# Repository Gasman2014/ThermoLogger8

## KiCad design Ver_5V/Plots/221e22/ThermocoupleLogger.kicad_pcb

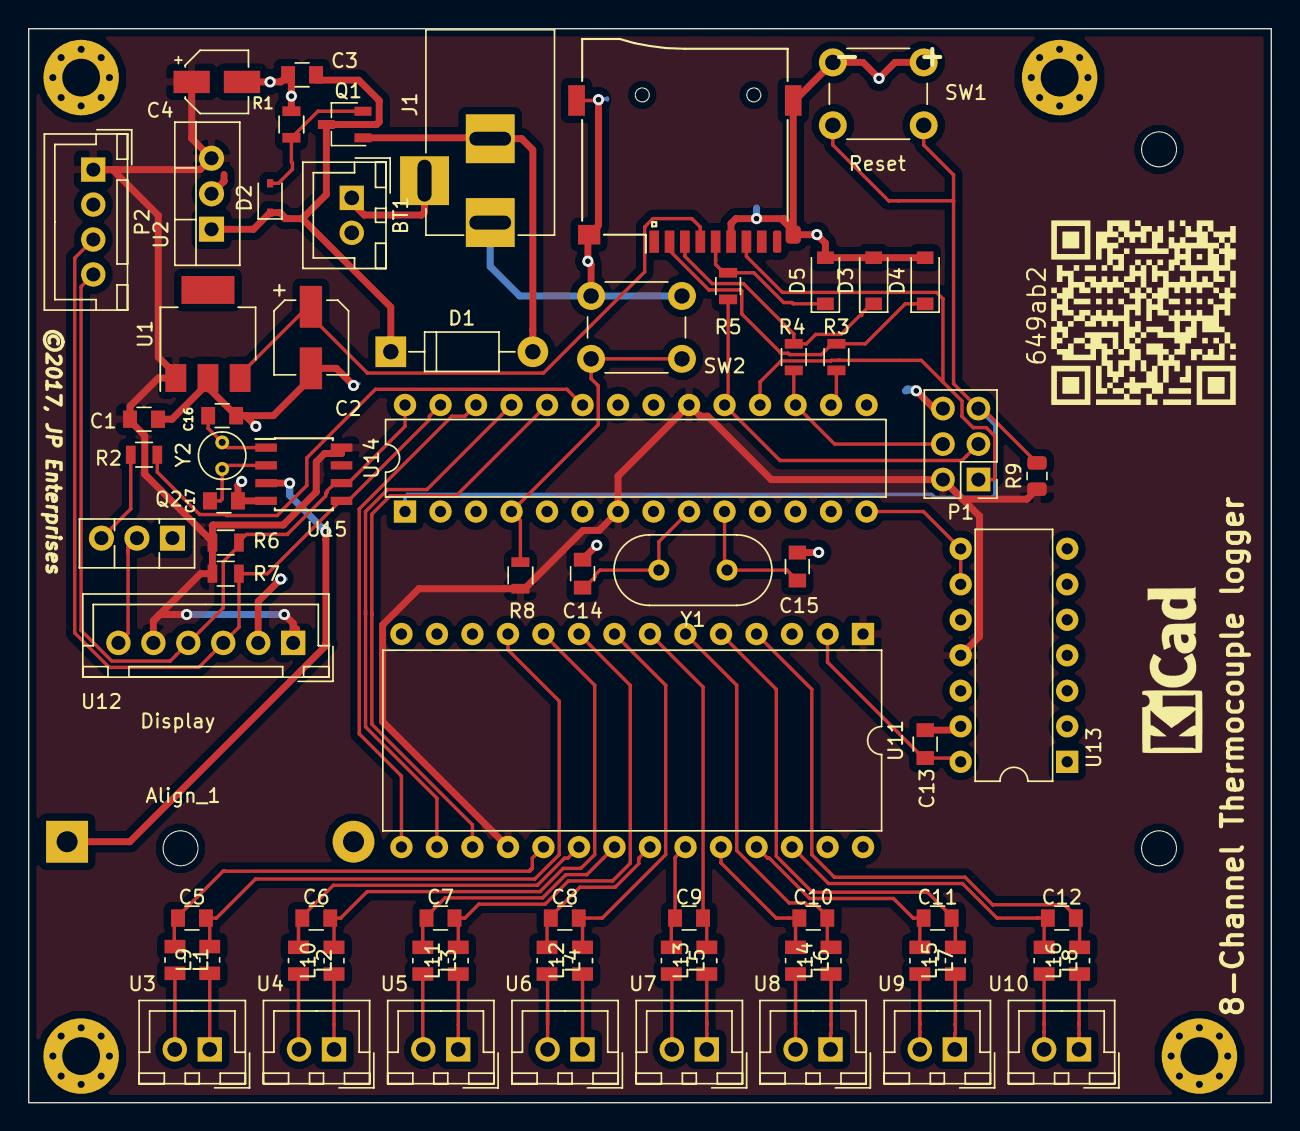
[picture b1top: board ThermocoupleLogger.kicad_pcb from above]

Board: 2 copper layers, 88.9 x 76.8 mm, 78 parts (1 on the bottom side), 63 nets.

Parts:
Align_1: Alignment_Hole_2.5mm
BT1: 9V; JST_XH_B02B-XH-A_02x2.50mm_Straight
BT2: Battery; Keystone_103_1x20mm-CoinCell
C1: 470nF; C_0805
C2: 47uF; CP_Elec_5x5.3
C3: 1uF; C_0805
C4: 10uF; CP_Elec_4x5.4
C5, C6, C7, C8, C9, C10, C11, C12, C13: 10nF; C_0805
C14, C15: 18pF; C_0805
C16, C17: 12pF; C_0805
D1: 1N4007; D_DO-41_SOD81_P10.16mm_Horizontal
D2: 9V; D_SOD-323
D3, D4, D5: 3.3V; D_SOD-123
J1: Barrel_Jack; BARREL_JACK
L1, L2, L3, L4, L5, L6, L7, L8, L9, L10, L11, L12, L13, L14, L15, L16: 150; L_0805_2012Metric
P1: CONN_02X03; Pin_Header_Straight_2x03_Pitch2.54mm
P2: Conn_01x04; JST_XH_B04B-XH-A_04x2.50mm_Straight
Q1: BS250; TSOT-23
Q2: BD139; TO-126_Vertical
QR*****: 649ab2
R1, R2, R8: 10K; R_0805
R3, R4, R5: 220R; R_0805
R6, R7: 5.1K; R_0805
R9: 10K; R_0805_2012Metric
Registration: Alignment_Hole_2.5mm
Registration#2: Alignment_Hole_2.5mm
SW1, SW2: SW_Push; SW_PUSH_6mm_h5mm
U1: LM3940; SOT-223
U2: 7805; TO-220_Vertical
U3, U4, U5, U6, U7, U8, U9, U10: TC_Connector; JST_XH_B02B-XH-A_02x2.50mm_Straight
U11: ADG407; DIP-28_W15.24mm
U12: I2C_20x4_DISPLAY; JST_XH_B06B-XH-A_06x2.50mm_Straight
U13: AD595; DIP-14_W7.62mm
U14: ATMEGA328P-PU; DIP-28_W7.62mm
U15: DS1307+; SOIC-8_3.9x4.9mm_Pitch1.27mm
XS1: SD_ebay-uSD-push/push_SMD; Conn_uSDcard
Y1: 16MHz; Crystal_HC49-U_Vertical
Y2: 32.768kHz; Crystal_Round_d3.0mm_Vertical

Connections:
3V3: C2.1, U1.3, XS1.4
5V0: C1.1, C4.1, P1.2, P2.1, R6.1, R7.1, R8.1, R9.1, U1.1, U2.3, U11.1, U11.18, U12.1, U12.5, U13.11, U14.7, U14.20, U15.8
9V0: C3.1, D1.1, D2.1, Q1.3, U2.1
/Thermocouple connectors/SA1: C5.1, L1.1, U11.19
/Thermocouple connectors/SA2: C6.1, L2.1, U11.20
/Thermocouple connectors/SA3: C7.1, L3.1, U11.21
/Thermocouple connectors/SA4: C8.1, L4.1, U11.22
/Thermocouple connectors/SA5: C9.1, L5.1, U11.23
/Thermocouple connectors/SA6: C10.1, L6.1, U11.24
/Thermocouple connectors/SA7: C11.1, L7.1, U11.25
/Thermocouple connectors/SA8: C12.1, L8.1, U11.26
/Thermocouple connectors/SB1: C5.2, L9.2, U11.11
/Thermocouple connectors/SB2: C6.2, L10.2, U11.10
/Thermocouple connectors/SB3: C7.2, L11.2, U11.9
/Thermocouple connectors/SB4: C8.2, L12.2, U11.8
/Thermocouple connectors/SB5: C9.2, L13.2, U11.7
/Thermocouple connectors/SB6: C10.2, L14.2, U11.6
/Thermocouple connectors/SB7: C11.2, L15.2, U11.5
/Thermocouple connectors/SB8: C12.2, L16.2, U11.4
/Thermocouple_PSU/Supply: D1.2, J1.2, Q1.1
B_LIGHT: R2.1, U14.23
DB_MUX: C13.2, U11.2, U13.14
GND: BT1.2, BT2.2, C1.2, C2.2, C3.2, C4.2, C13.1, C14.1, C15.1, C16.2, C17.2, D3.2, D4.2, D5.2, J1.1, P1.6, P2.2, Q2.1, R1.2, SW1.2, SW2.2, U1.2, U2.2, U11.12, U11.28, U12.2, U13.1, U13.4, U13.7, U13.13, U14.8, U14.22, U15.4, XS1.6
MISO: P1.1, U14.18, XS1.7
MOSI: P1.4, R4.1, U14.17
unnamed: BT1.1, J1.3
unnamed: BT2.1, U15.3
unnamed: C14.2, U14.9, Y1.2
unnamed: C15.2, U14.10, Y1.1
unnamed: C16.1, U15.1, Y2.1
unnamed: C17.1, U15.2, Y2.2
unnamed: D2.2, Q1.2, R1.1
unnamed: D3.1, R4.2, XS1.3
unnamed: D4.1, R3.2, XS1.2
unnamed: D5.1, R5.2, XS1.5
unnamed: L1.2, U3.2
unnamed: L2.2, U4.2
unnamed: L3.2, U5.2
unnamed: L4.2, U6.2
unnamed: L5.2, U7.2
unnamed: L6.2, U8.2
unnamed: L7.2, U9.2
unnamed: L8.2, U10.2
unnamed: L9.1, U3.1
unnamed: L10.1, U4.1
unnamed: L11.1, U5.1
unnamed: L12.1, U6.1
unnamed: L13.1, U7.1
unnamed: L14.1, U8.1
unnamed: L15.1, U9.1
unnamed: L16.1, U10.1
unnamed: Q2.2, U12.6
unnamed: Q2.3, R2.2
unnamed: R8.2, SW2.1, U14.4
RESET: P1.5, R9.2, SW1.1, U14.1
SCK: P1.3, R5.1, U14.19
SCL: P2.4, R6.2, U12.4, U14.28, U15.6
SDA: P2.3, R7.2, U12.3, U14.27, U15.5
SLCT0: U11.17, U14.24
SLCT1: U11.16, U14.25
SLCT2: U11.15, U14.26
SS: R3.1, U14.16
TEMP: U13.8, U13.9, U14.14

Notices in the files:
Ver_5V/Plots/221e22/ThermocoupleLogger.kicad_pcb:
©2017, JP Enterprises
